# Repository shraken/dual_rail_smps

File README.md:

# dual_rail_smps

A dual +15/-15V rail SMPS test board using the TI tps61170 and tps63700 designed in KiCad.  Includes source, BOM, and zipped manufacturing and stencil files.

The kicad_libs [library](https://github.com/shraken/kicad_libs) is required.

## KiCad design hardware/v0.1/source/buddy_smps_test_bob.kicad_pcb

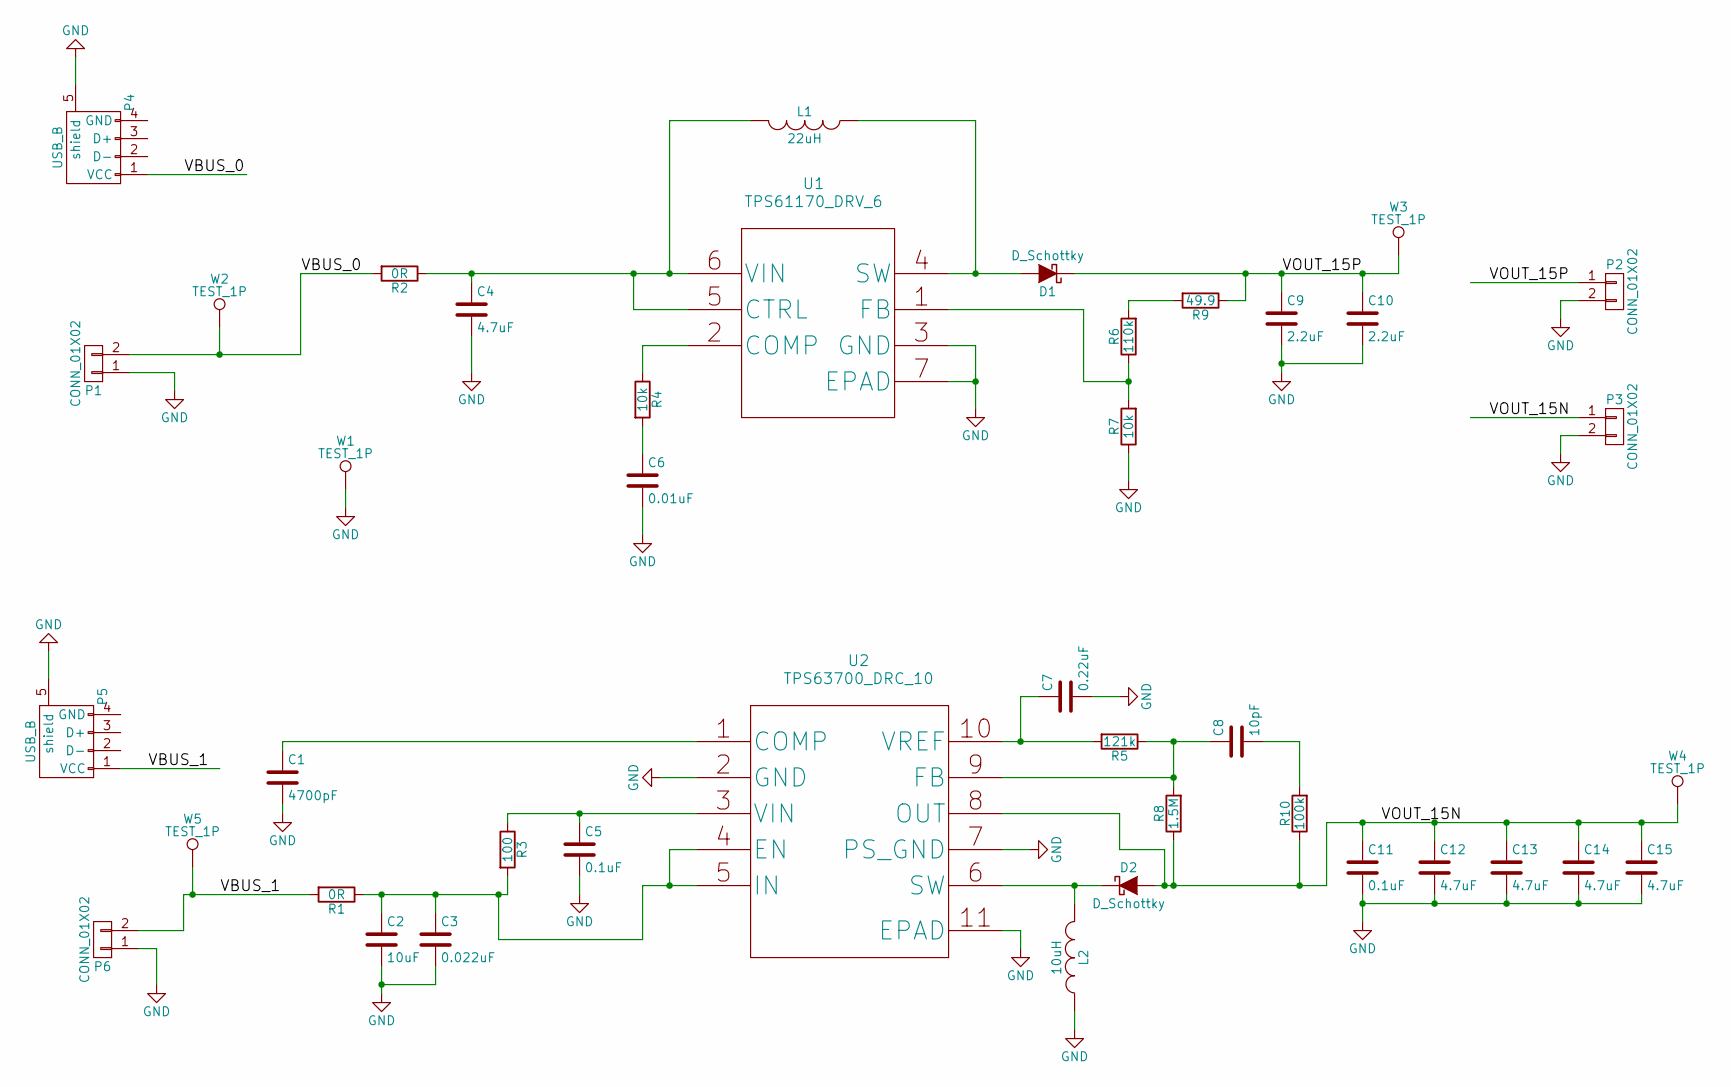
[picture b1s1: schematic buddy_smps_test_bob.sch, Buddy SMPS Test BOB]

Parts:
C1: 4700pF; C_0603_HandSoldering
C2: 10uF; C_0805_HandSoldering
C3: 0.022uF; C_0603_HandSoldering
C4: 4.7uF; C_0805_HandSoldering
C5: 0.1uF; C_0603_HandSoldering
C6: 0.01uF; C_0603_HandSoldering
C7: 0.22uF; C_0603_HandSoldering
C8: 10pF; C_0603_HandSoldering
C9, C10: 2.2uF; R_1206_HandSoldering
C11: 0.1uF; C_0805_HandSoldering
C12, C13, C14, C15: 4.7uF; C_1206_HandSoldering
D1: D_Schottky; D_SOD-123
D2: D_Schottky; DO-219AB
L1: 22uH; D6030-220-R
L2: 10uH; CDRH5D18NP-100NC
P1, P2, P3, P6: CONN_01X02; Pin_Header_Straight_1x02_Pitch2.54mm
P4, P5: USB_B; microb_usb_top_mount
R1, R2: 0R; R_1206_HandSoldering
R3: 100; R_0603_HandSoldering
R4, R7: 10k; R_0603_HandSoldering
R5: 121k; R_0603_HandSoldering
R6: 110k; R_0603_HandSoldering
R8: 1.5M; R_0603_HandSoldering
R9: 49.9; R_0603_HandSoldering
R10: 100k; R_0603_HandSoldering
U1: TPS61170_DRV_6
U2: TPS63700_DRC_10
W1, W2, W3, W4, W5: TEST_1P; Test_Point_Keystone_5000-5004_Miniature

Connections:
/VBUS_0: P1.2, P4.1 (VCC), R2.2, W2.1
/VBUS_1: P5.1 (VCC), P6.2, R1.2, W5.1
/VOUT_15N: C11.1, C12.1, C13.1, C14.1, C15.1, D2.2 (A), P3.1, R8.1, R10.1, U2.8 (OUT), W4.1
/VOUT_15P: C9.1, C10.1, D1.1 (K), P2.1, R9.1, W3.1
GND: C1.2, C2.2, C3.2, C4.2, C5.2, C6.2, C7.2, C9.2, C10.2, C11.2, C12.2, C13.2, C14.2, C15.2, L2.1, P1.1, P2.2, P3.2, P4.5 (shield), P5.5 (shield), P6.1, R7.1, U1.3 (GND), U1.7 (EPAD), U2.2 (GND), U2.7 (PS_GND), U2.11 (EPAD), W1.1
unnamed: C1.1, U2.1 (COMP)
unnamed: C2.1, C3.1, R1.1, R3.2, U2.4 (EN), U2.5 (IN)
unnamed: C4.1, L1.2, R2.1, U1.5 (CTRL), U1.6 (VIN)
unnamed: C5.1, R3.1, U2.3 (VIN)
unnamed: C6.1, R4.2
unnamed: C7.1, R5.2, U2.10 (VREF)
unnamed: C8.1, R5.1, R8.2, U2.9 (FB)
unnamed: C8.2, R10.2
unnamed: D1.2 (A), L1.1, U1.4 (SW)
unnamed: D2.1 (K), L2.2, U2.6 (SW)
unnamed: R4.1, U1.2 (COMP)
unnamed: R6.1, R7.2, U1.1 (FB)
unnamed: R6.2, R9.2

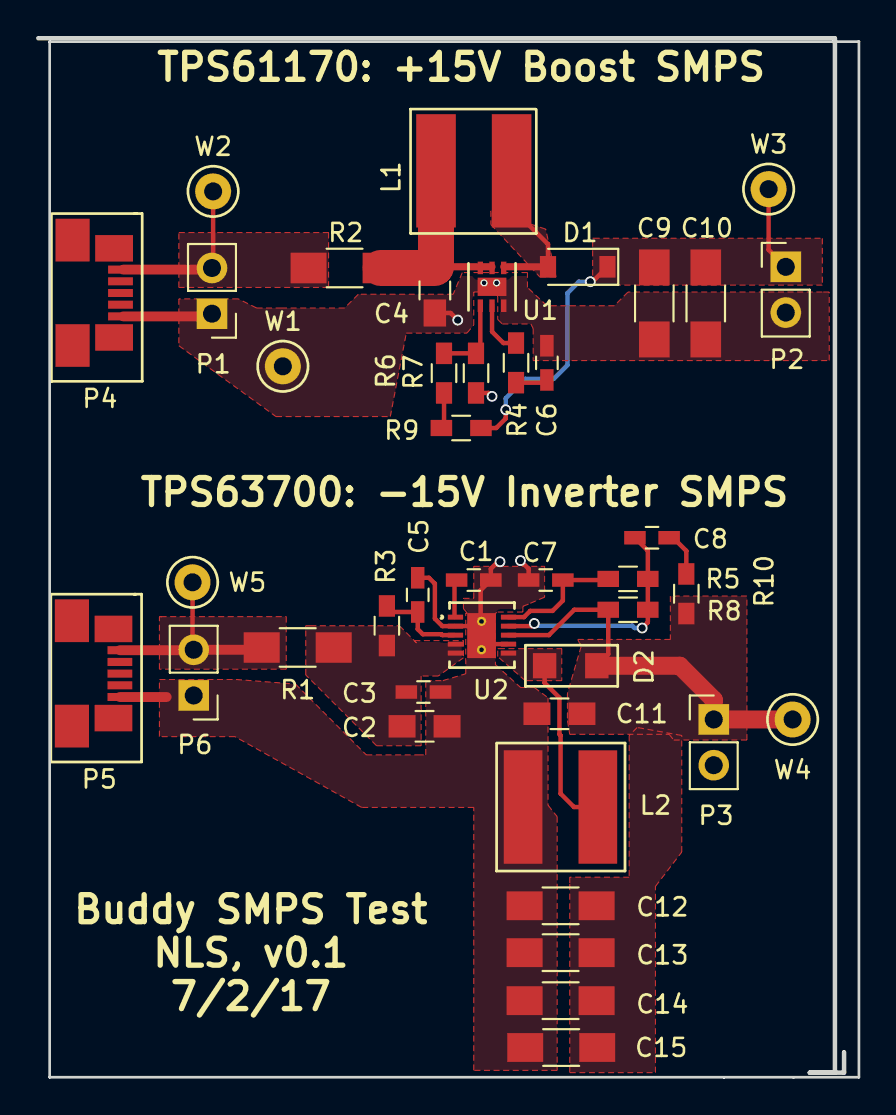
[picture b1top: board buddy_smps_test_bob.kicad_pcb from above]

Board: 2 copper layers, 45.5 x 57.7 mm, 42 parts (0 on the bottom side), 18 nets.

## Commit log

2017-12-03 first commit: add buddy_smps_test_bob board files
2017-12-03 add image of v0.1 board
2017-12-03 fix bad image ref
2017-12-03 make relative image link and shrink 50%

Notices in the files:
parts and their libraries:
Copyright 2016 Accelerated Designs. All rights reserved.
